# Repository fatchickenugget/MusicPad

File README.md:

# MusicPad

A music application UI Macropad

### Purpose

I made this macropad for Hack Club's Highway using their [Hackpad Tutorial](https://hackpad.hackclub.com/). It's meant to be used as an accompaniment to music applications, primarily Youtube Music (which I use), as a physical UI. I like to listen to music 

### Features
- An OLED meant to display info such as:
  - Song name/duration
  - Whether song is played/paused
  - Whether shuffle or loop (playlist or song) is on
  - More ideas in the future if I come up with any :)
- A rotary encoder switch that changes the volume and mutes the music application when pressed
- Keys for rewind/prev track, play/pause, fast forward/next track, loop, and shuffle
- A Mini-E LED which, for now, is meant to serve as an indicator that the macropad is on
- QMK Firmware

### BOM

- 5x Cherry MX Switches
- 1x EC11 Rotary encoder
- 1x SK6812 MINI LED
- 1x Seeed XIAO RP2040
- 1x 0.91 inch OLED display
- 5x Blank DSA Keycaps
- 6x Through-hole 1n4148 Diodes
- 4x M3x16 Screws
- 4x M3 Heatset Inserts

### Screenshots:
**Schematic**

**PCB**   

**Case**

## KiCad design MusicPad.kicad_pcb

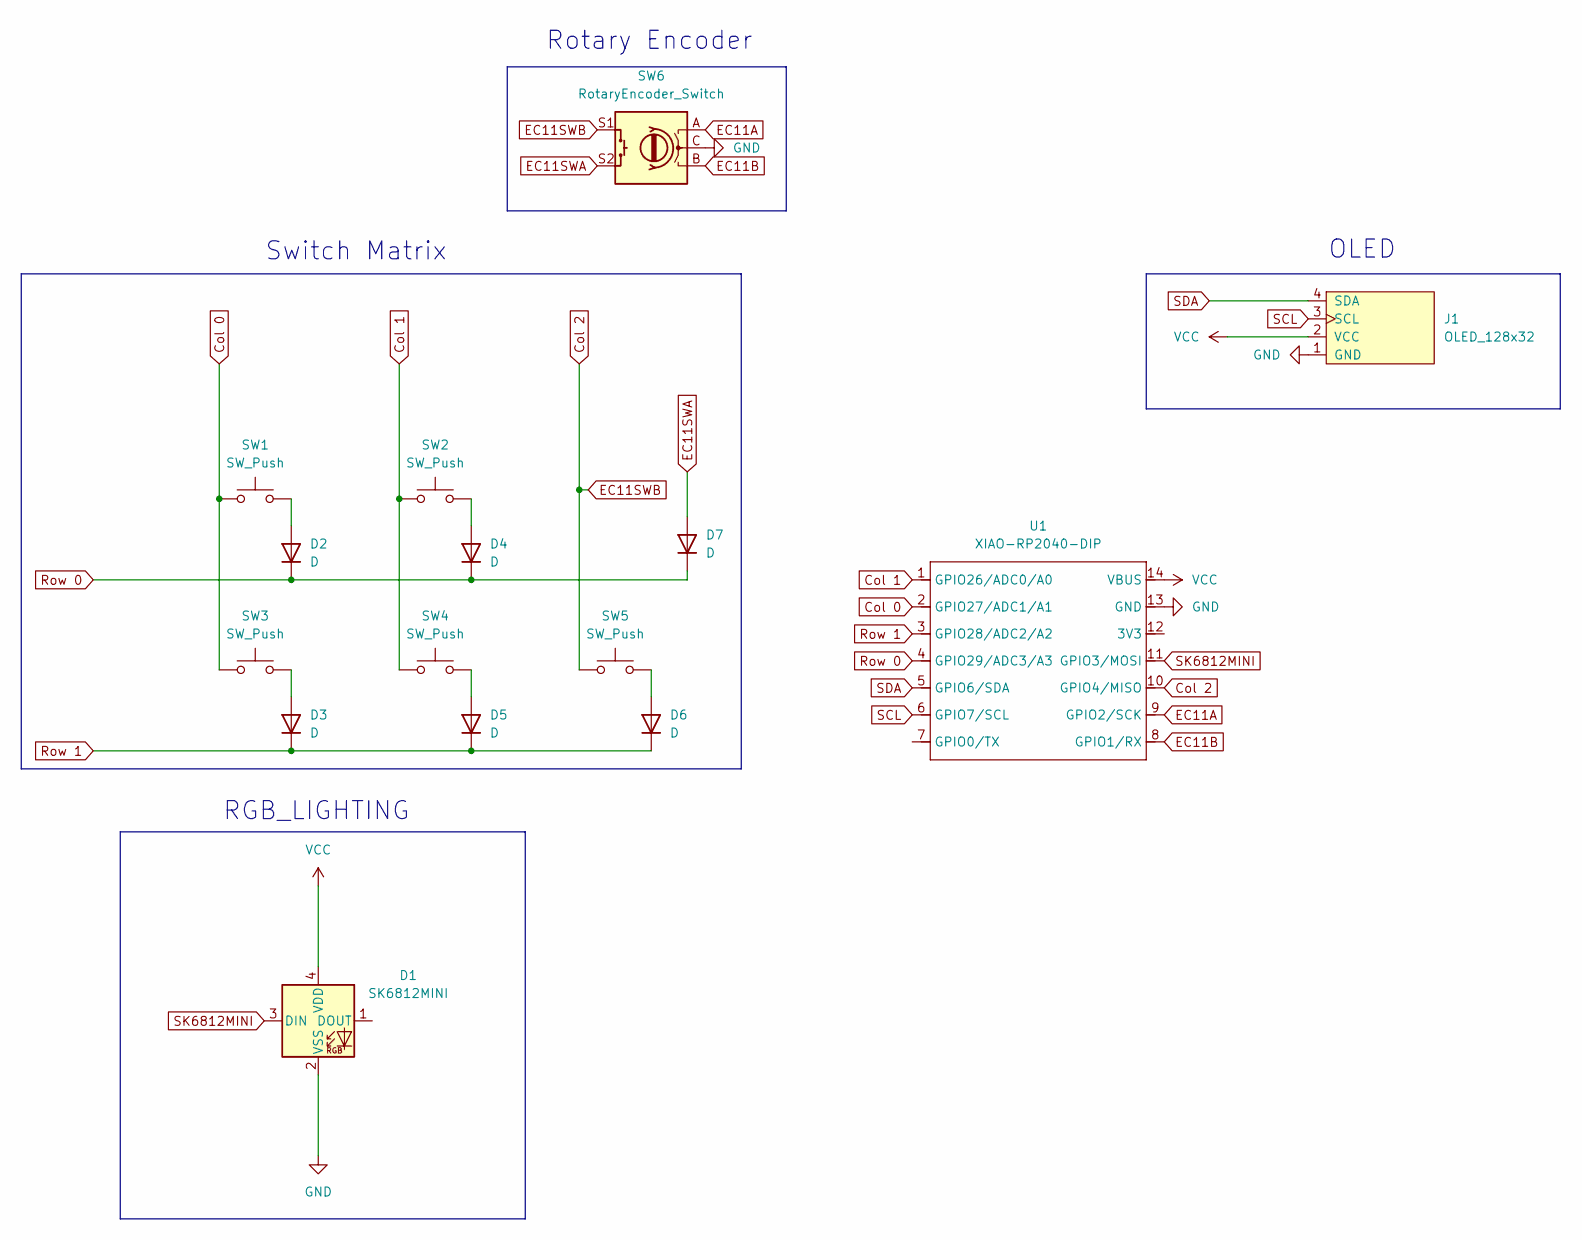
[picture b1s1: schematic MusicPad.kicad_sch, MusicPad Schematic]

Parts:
D1: SK6812MINI; LED_SK6812MINI_PLCC4_3.5x3.5mm_P1.75mm
D2, D3, D4, D5, D6, D7: D; D_DO-35_SOD27_P7.62mm_Horizontal
J1: OLED_128x32
SW1, SW2, SW3, SW4, SW5: SW_Push; SW_Cherry_MX_1.00u_PCB
SW6: RotaryEncoder_Switch; RotaryEncoder_Alps_EC11E-Switch_Vertical_H20mm
U1: XIAO-RP2040-DIP

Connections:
Col 0: SW1.1, SW3.1, U1.2 (GPIO27/ADC1/A1)
Col 1: SW2.1, SW4.1, U1.1 (GPIO26/ADC0/A0)
Col 2: SW5.1, SW6.S1, U1.10 (GPIO4/MISO)
EC11A: SW6.A, U1.9 (GPIO2/SCK)
EC11B: SW6.B, U1.8 (GPIO1/RX)
EC11SWA: D7.2 (A), SW6.S2
GND: D1.2 (VSS), J1.1 (GND), SW6.C, U1.13 (GND)
unnamed: D2.2 (A), SW1.2
unnamed: D3.2 (A), SW3.2
unnamed: D4.2 (A), SW2.2
unnamed: D5.2 (A), SW4.2
unnamed: D6.2 (A), SW5.2
Row 0: D2.1 (K), D4.1 (K), D7.1 (K), U1.4 (GPIO29/ADC3/A3)
Row 1: D3.1 (K), D5.1 (K), D6.1 (K), U1.3 (GPIO28/ADC2/A2)
SCL: J1.3 (SCL), U1.6 (GPIO7/SCL)
SDA: J1.4 (SDA), U1.5 (GPIO6/SDA)
SK6812MINI: D1.3 (DIN), U1.11 (GPIO3/MOSI)
VCC: D1.4 (VDD), J1.2 (VCC), U1.14 (VBUS)

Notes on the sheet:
OLED
Rotary Encoder
Switch Matrix
RGB_LIGHTING

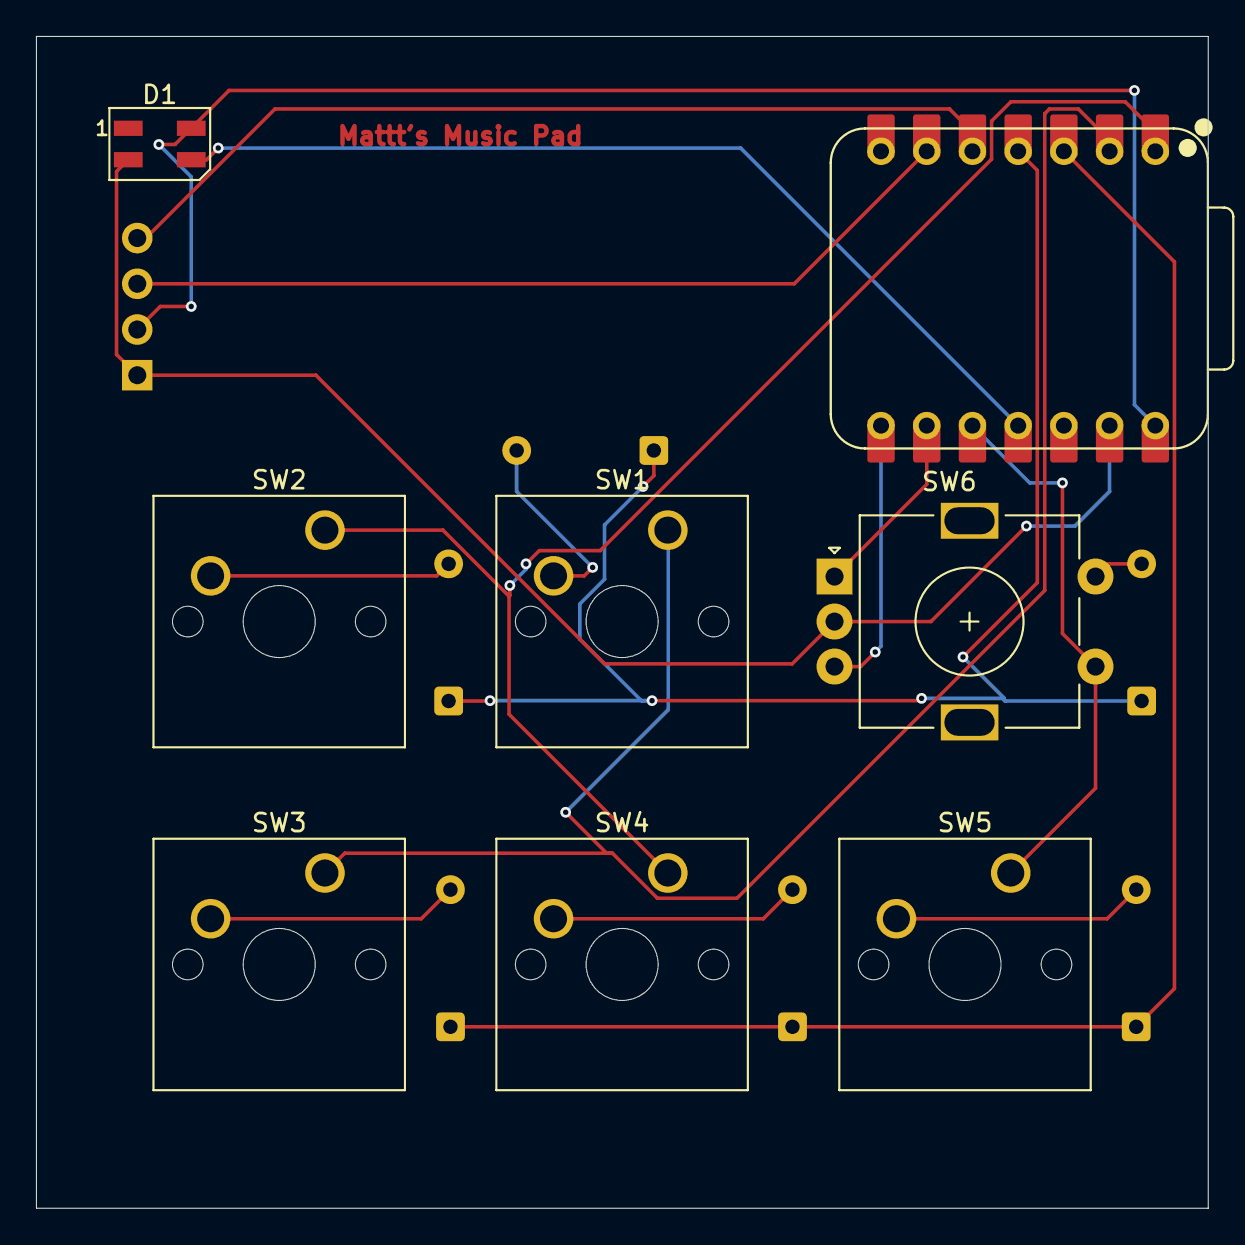
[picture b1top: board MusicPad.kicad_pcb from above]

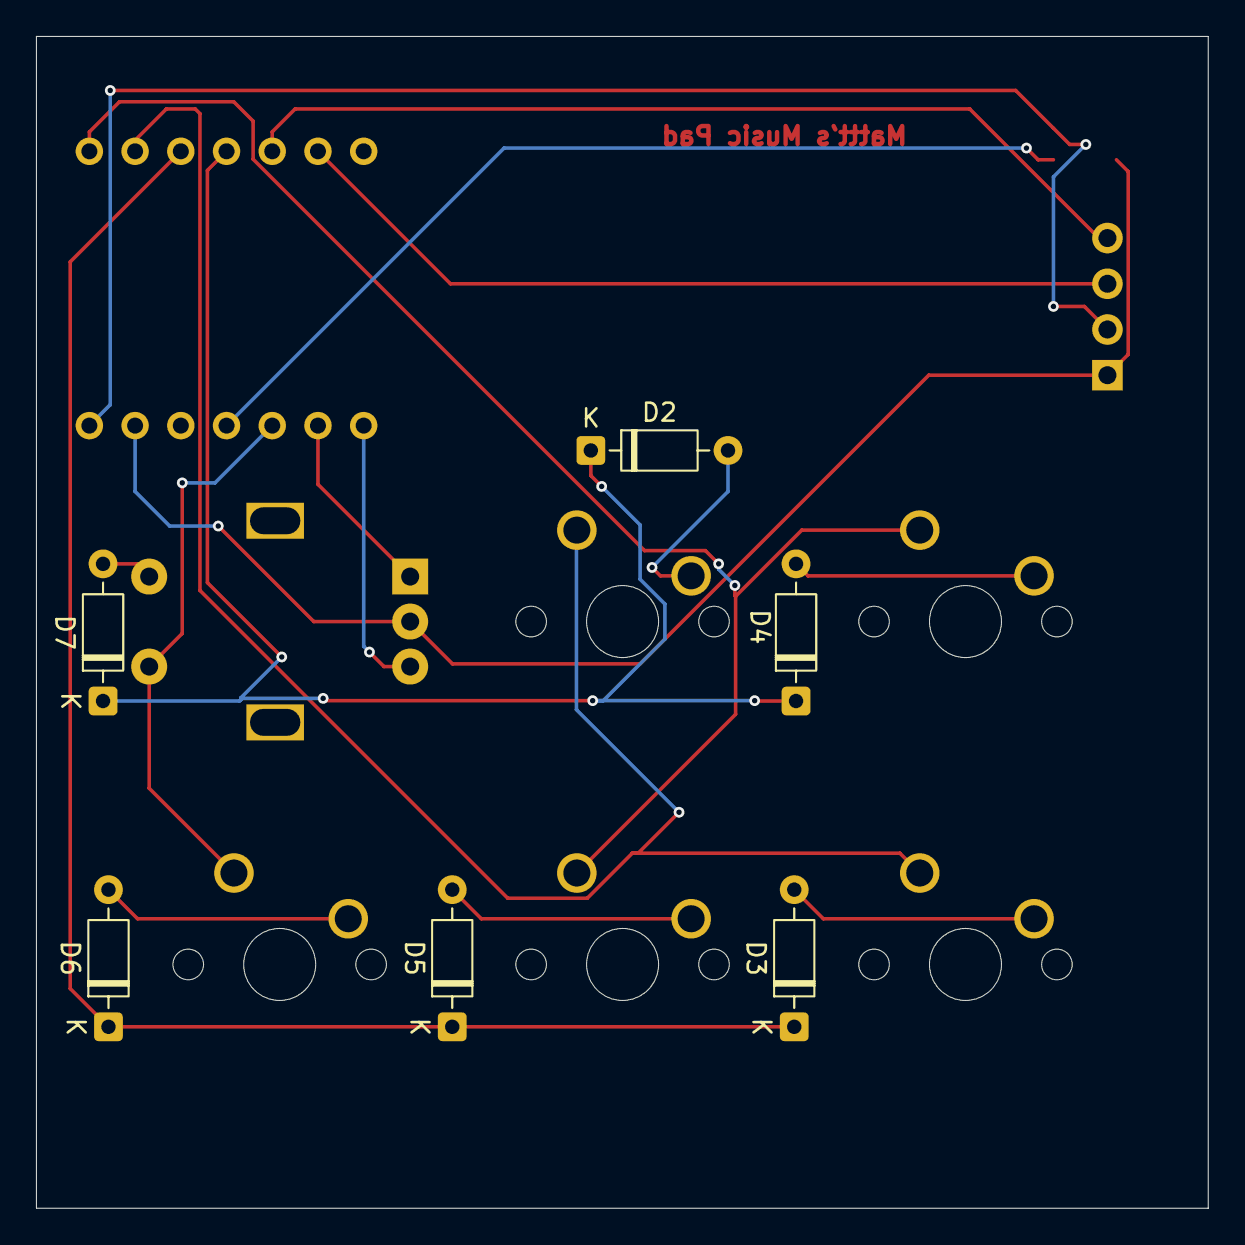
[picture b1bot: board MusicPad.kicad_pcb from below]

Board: 2 copper layers, 65.1 x 65.1 mm, 15 parts (6 on the bottom side), 18 nets.

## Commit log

2025-06-05 Update Journal.md
    wrote everything I've done thus far
2025-06-07 Initial remote commmit / update folder files
2025-06-07 Added Readme and Journal
2025-06-21 reorganized repository, added firmware
2025-06-21 removed extraneous musicpad folder
2025-06-21 added production files
2025-06-21 Added back libraries
2025-06-21 stated how long this took
2025-06-21 Update Journal.md
    Titled work days
